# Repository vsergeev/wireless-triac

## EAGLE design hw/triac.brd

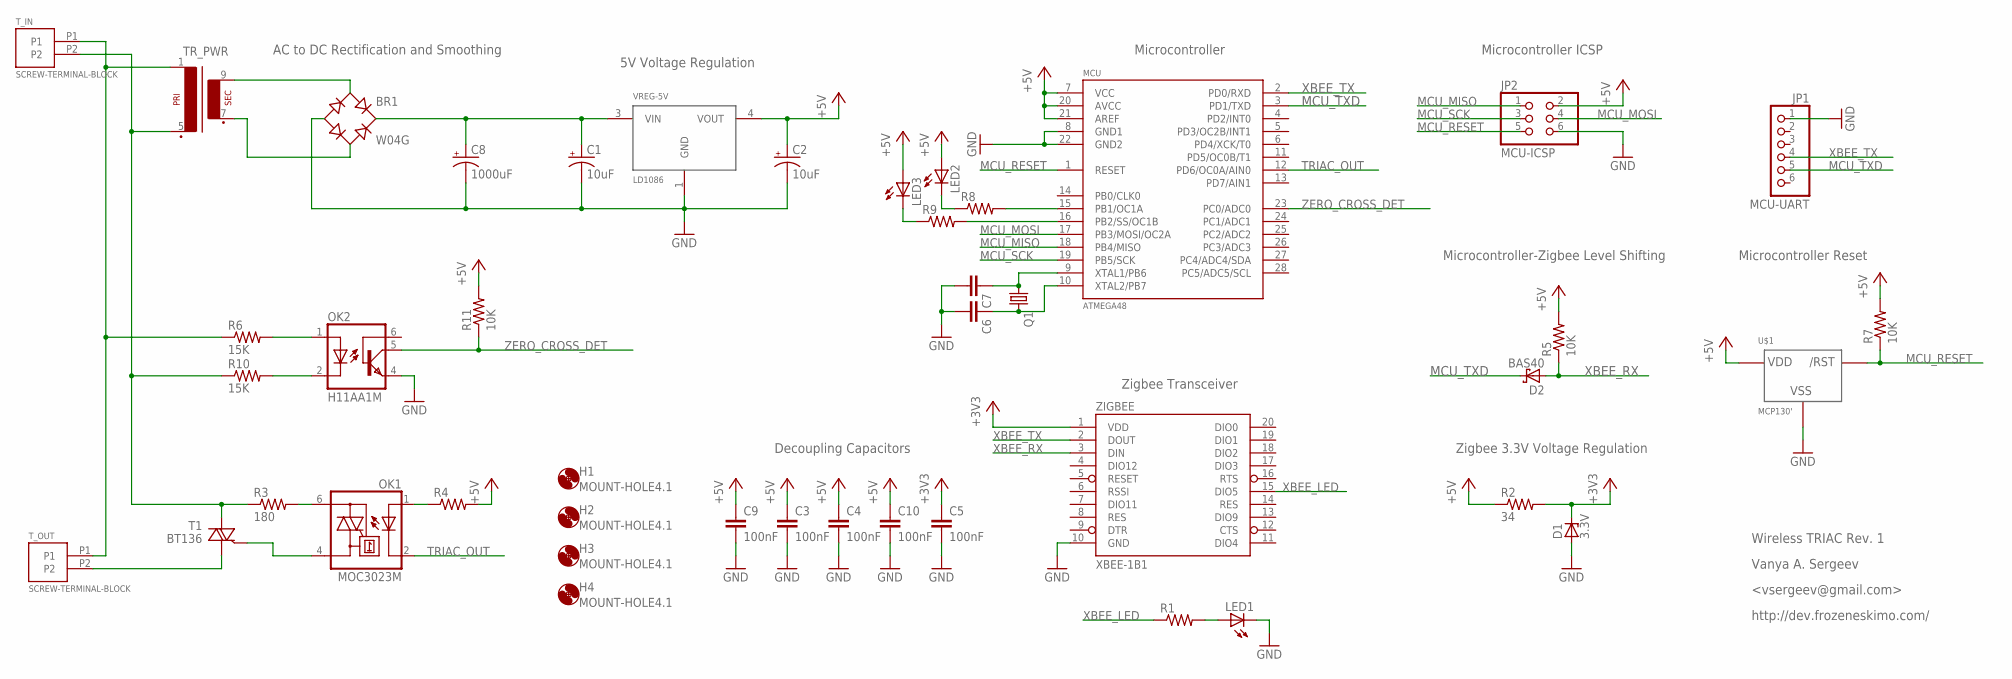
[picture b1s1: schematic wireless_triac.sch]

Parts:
BR1: W04G; WOG
C1, C2: 10uF; E2,5-5
C3, C4, C5, C9, C10: 100nF; C0805
C6, C7: C-EUC0805; C0805
C8: 1000uF; E5-13
D1: 3.3V; SOT23
D2: BAS40; SOT23
H1, H2, H3, H4: MOUNT-HOLE4.1; 4,1
JP1: MCU-UART; 1X06
JP2: MCU-ICSP; 2X03
LED1, LED2, LED3: LEDCHIPLED_0805; CHIPLED_0805
MCU: ATMEGA48; DIL28-3
OK1: MOC3023M; DIL06
OK2: H11AA1M; DIL06
Q1: CRYSTALHC49UP; HC49UP
R1, R4, R8, R9: R-US_R0805; R0805
R2: 34; R0805
R3: 180; 0204/7
R5, R7, R11: 10K; R0805
R6, R10: 15K; 0204/7
T1: BT136; TO220AB
TR_PWR: EI30-1
T_IN: SCREW-TERMINAL-BLOCK; TERMINAL-BLOCK
T_OUT: SCREW-TERMINAL-BLOCK; TERMINAL-BLOCK
U$1: MCP130'; TO92
VREG-5V: LD1086; DPACK
ZIGBEE: XBEE-1B1; XBEE-1

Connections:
+3V3: C5.1, D1.3 (C), R2.2, ZIGBEE.1 (VDD)
+5V: C2.+, C3.1, C4.1, C9.1, C10.1, JP2.2, LED2.A, LED3.A, MCU.7 (VCC), MCU.20 (AVCC), MCU.21 (AREF), R2.1, R4.2, R5.2, R7.2, R11.2, U$1.2 (VDD), VREG-5V.4 (VOUT)
DC+: BR1.+, C1.+, C8.+, VREG-5V.3 (VIN)
GND: BR1.-, C1.-, C2.-, C3.2, C4.2, C5.2, C6.2, C7.2, C8.-, C9.2, C10.2, D1.1 (A), JP1.1, JP2.6, LED1.C, MCU.8 (GND1), MCU.22 (GND2), OK2.4 (EMI), U$1.3 (VSS), VREG-5V.1 (GND), ZIGBEE.10 (GND)
MCU_MISO: JP2.1, MCU.18 (PB4/MISO)
MCU_MOSI: JP2.4, MCU.17 (PB3/MOSI/OC2A)
MCU_RESET: JP2.5, MCU.1 (RESET), R7.1, U$1.1 (/RST)
MCU_SCK: JP2.3, MCU.19 (PB5/SCK)
MCU_TXD: D2.3 (C), JP1.5, MCU.3 (PD1/TXD)
unnamed: OK1.6 (A2), R3.2
unnamed: BR1.AC1, TR_PWR.9 (S4)
unnamed: BR1.AC2, TR_PWR.7 (S3)
unnamed: C6.1, MCU.10 (XTAL2/PB7), Q1.2
unnamed: T1.1 (A1), T_OUT.P2
unnamed: OK1.4 (A1), T1.3 (G)
unnamed: OK1.1 (A), R4.1
unnamed: OK2.2 (C), R10.2
unnamed: OK2.1 (A), R6.2
unnamed: LED1.A, R1.2
unnamed: LED2.C, R8.1
unnamed: MCU.15 (PB1/OC1A), R8.2
unnamed: C7.1, MCU.9 (XTAL1/PB6), Q1.1
unnamed: MCU.16 (PB2/SS/OC1B), R9.2
unnamed: LED3.C, R9.1
unnamed: R6.1, TR_PWR.1, T_IN.P1, T_OUT.P1
unnamed: R3.1, R10.1, T1.2 (A2), TR_PWR.5 (P2), T_IN.P2
TRIAC_OUT: MCU.12 (PD6/OC0A/AIN0), OK1.2 (C)
XBEE_LED: R1.1, ZIGBEE.15 (DIO5)
XBEE_RX: D2.1 (A), R5.1, ZIGBEE.3 (DIN)
XBEE_TX: JP1.4, MCU.2 (PD0/RXD), ZIGBEE.2 (DOUT)
ZERO_CROSS_DET: MCU.23 (PC0/ADC0), OK2.5 (COL), R11.1

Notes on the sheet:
AC to DC Rectification and Smoothing
5V Voltage Regulation
Microcontroller
Zigbee Transceiver
Zigbee 3.3V Voltage Regulation
Decoupling Capacitors
Microcontroller ICSP
Microcontroller-Zigbee Level Shifting
Microcontroller Reset
Wireless TRIAC Rev. 1
Vanya A. Sergeev
<vsergeev@gmail.com>
http://dev.frozeneskimo.com/

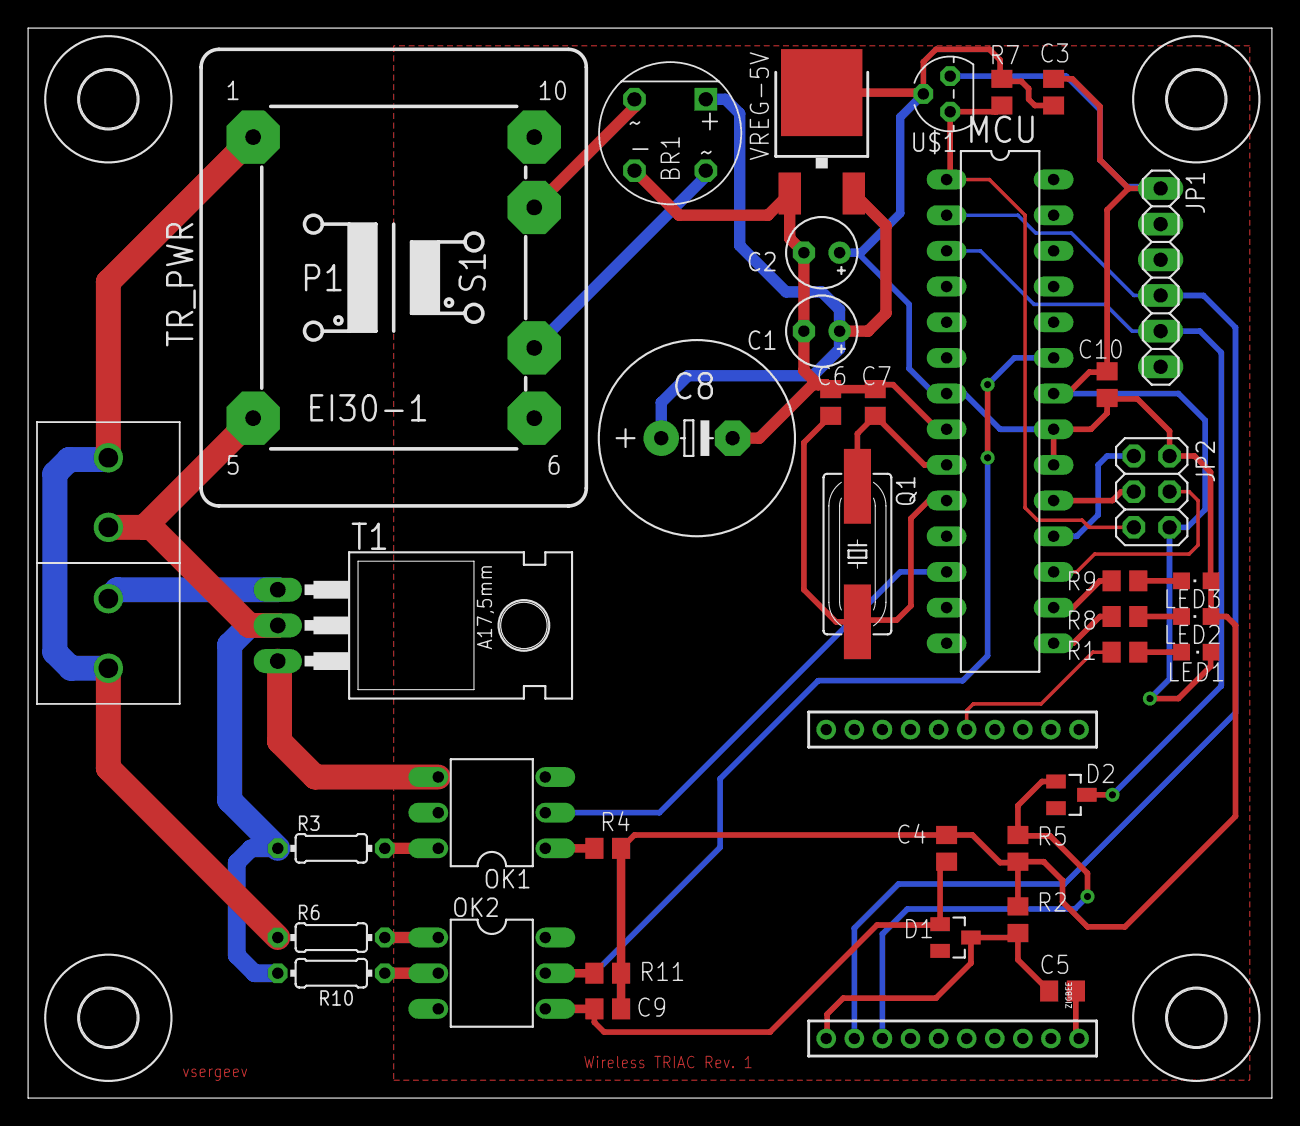
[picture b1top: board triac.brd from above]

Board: 2 copper layers, 88.6 x 76.2 mm, 44 parts (0 on the bottom side), 31 nets.

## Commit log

2012-03-06 renamed hw files
